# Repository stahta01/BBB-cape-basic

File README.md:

# BBB-cape-basic
Basic cape design for Beaglebone Black

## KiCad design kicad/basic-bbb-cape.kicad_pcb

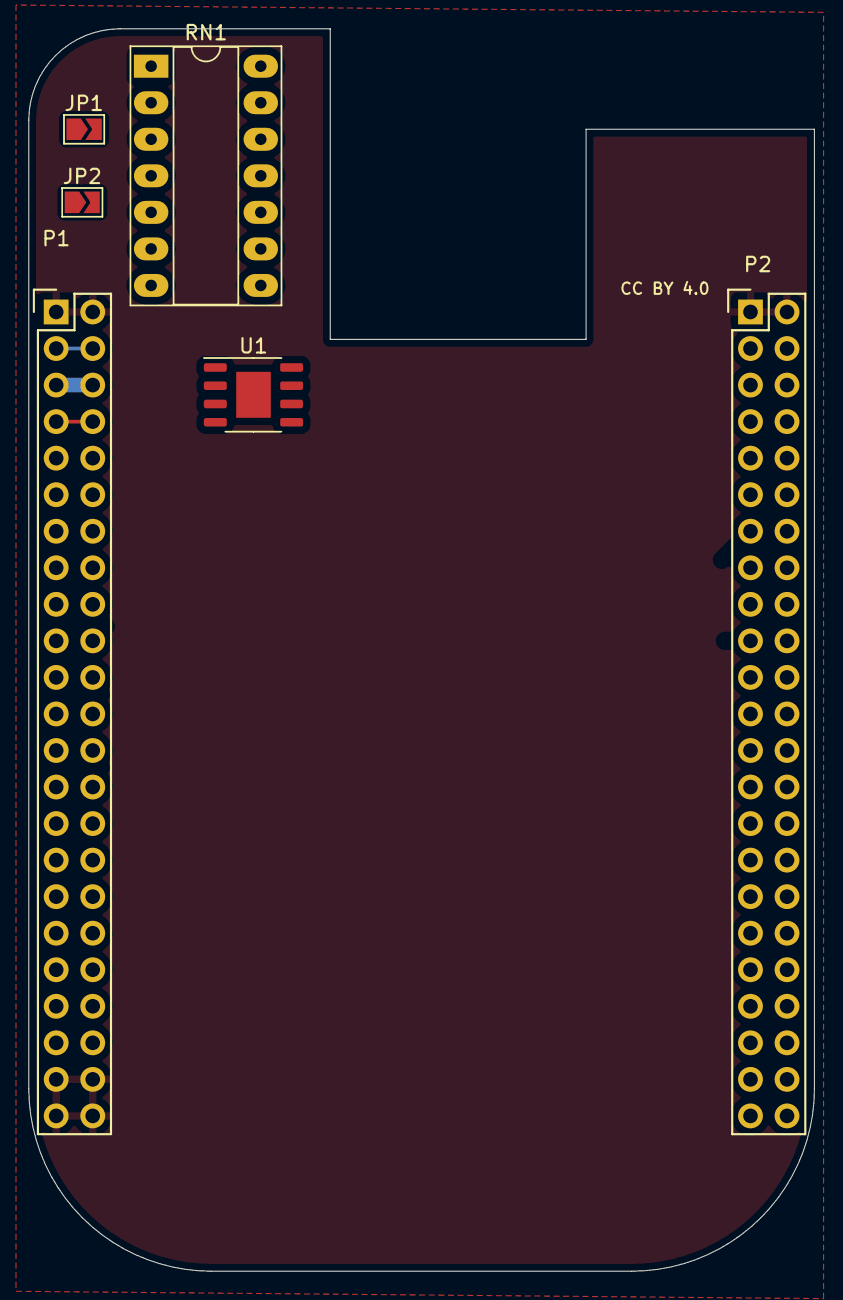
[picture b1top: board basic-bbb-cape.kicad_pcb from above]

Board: 2 copper layers, 54.6 x 86.4 mm, 6 parts (0 on the bottom side), 11 nets.

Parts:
JP1, JP2: SolderJumper_2_Open; SolderJumper-2_P1.3mm_Open_TrianglePad1.0x1.5mm
P1, P2: BeagleBone_Black_Header; Socket_BeagleBone_Black
RN1: R_Pack07; DIP-14_W7.62mm_Socket_LongPads
U1: CAT24C32YI-GT3; HTSOP-8-1EP_3.9x4.9mm_P1.27mm_EP2.4x3.2mm

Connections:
+3V3: P1.3, P1.4, RN1.1 (R1.1), RN1.2 (R2.1), RN1.3 (R3.1), RN1.4 (R4.1), RN1.5 (R5.1), RN1.6 (R6.1), RN1.7 (R7.1), U1.8 (VCC)
+5V: P1.5, P1.6
Earth: P1.1, P1.2, P1.43, P1.44, P1.45, P1.46, P2.1, P2.2
GNDD: JP1.1 (A), JP2.1 (A), U1.4 (GND)
I2C2_SCL: RN1.8 (R7.2), U1.6 (SCL)
I2C2_SDA: RN1.9 (R6.2), U1.5 (SDA)
unnamed: JP1.2 (B), RN1.13 (R2.2), U1.1 (A0)
unnamed: JP2.2 (B), RN1.12 (R3.2), U1.2 (A1)
unnamed: RN1.10 (R5.2), U1.7 (WP)
unnamed: RN1.11 (R4.2), U1.3 (A2)
SYS_5V: P1.7, P1.8

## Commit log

2022-05-09 git: Add to ignore list
2022-05-09 Add starting kicad project based on
    https://github.com/wie-niet/doorlockd-PCB-BBB with a lot removed.
2022-05-10 Add kicad/custom_lib/pwr_BeagleBone.lib
2022-05-10 kicad: Multiple changes including adding
    sym-lib-table,
    Beaglebone_black_p8.kicad_sym, and
    Beaglebone_black_p9.kicad_sym.
2022-05-10 Move EEPROM on schematic
2022-05-10 Add resistor pack/network
2022-05-10 Add Jumpers and test point
2022-05-10 Placed RP on PCB; do not like it best to turn 180 degrees.
2022-05-10 Rotate RP1 and U1 180 degrees
2022-05-10 Add solder jumper to PCB
2022-05-11 Add kicad/custom_lib/r_pack_eeprom.kicad_sym
2022-05-11 Update schematic and PCB
2022-05-12 Move RP1 socket
2022-05-12 Resize schematic to 8x11 inch and reset PCH closer to defaults

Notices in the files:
kicad/basic-bbb-cape.kicad_pcb:
CC BY 4.0
